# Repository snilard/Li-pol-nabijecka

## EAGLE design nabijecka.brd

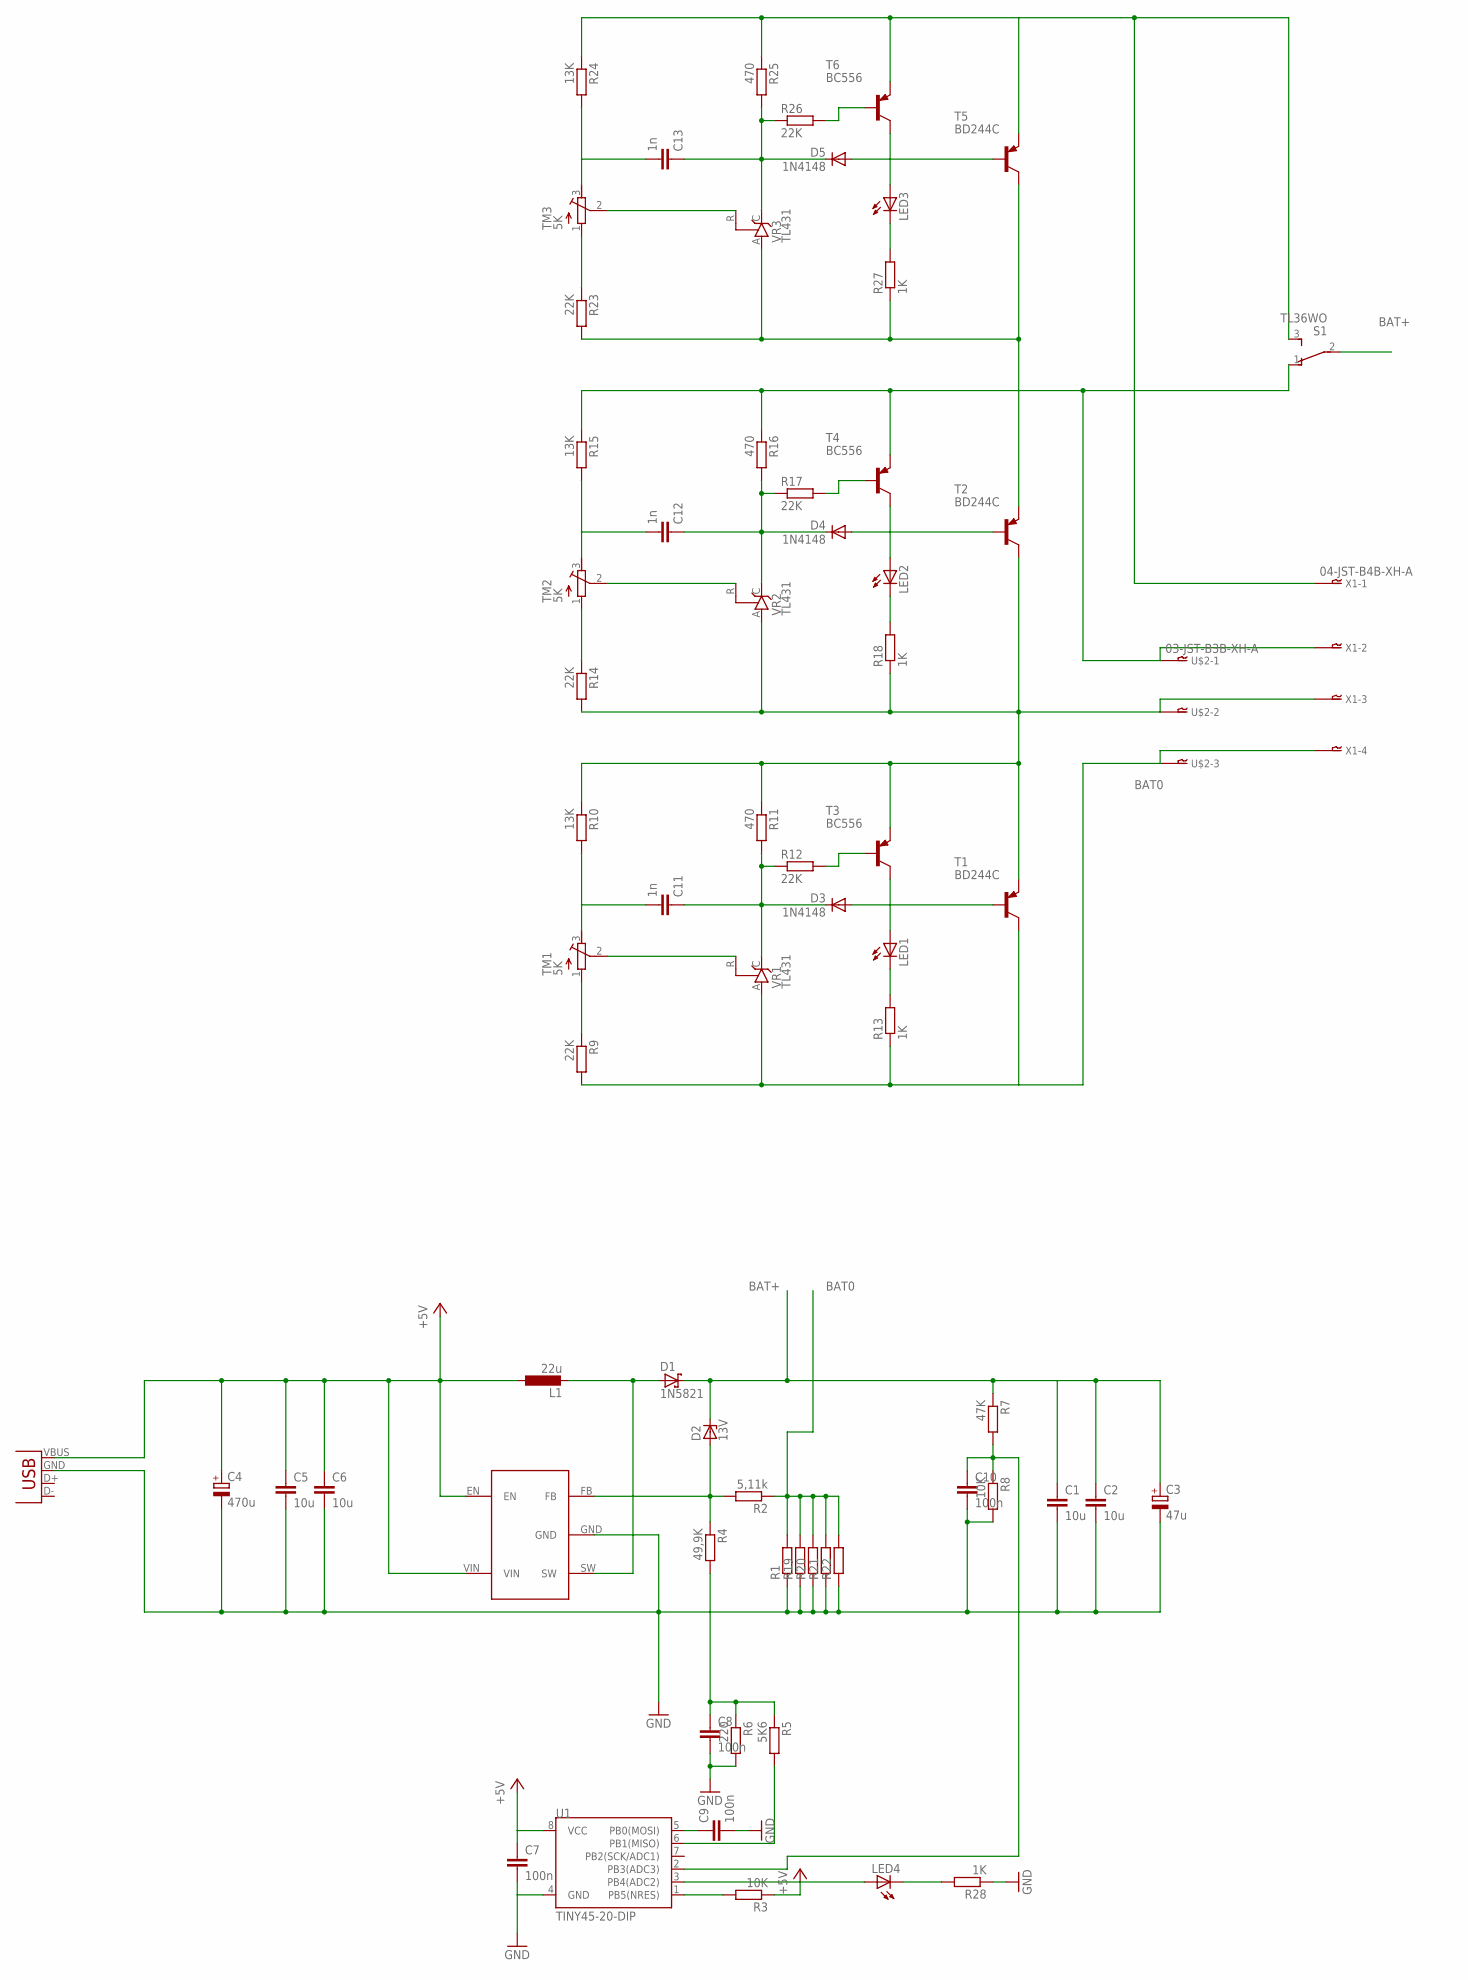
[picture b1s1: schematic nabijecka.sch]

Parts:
C1, C2, C5, C6: 10u; C1206
C3: 47u; E3,5-8
C4: 470u; E3,5-8
C7, C9: 100n; C0805
C8, C10: 100n; C1206
C11, C12, C13: 1n; C1206
D1: 1N5821; DO35-7
D2: 13V; SOD80C
D3, D4, D5: 1N4148; SOD80C
JP2: USB-A-H
L1: 22u; POWER-CHOKE_WE-TPC
LED1, LED2, LED3, LED4: LED3MM
R1, R19, R20, R21, R22: R-EU_0204/7; 0204/7
R2: 5,11k; 0204/5
R3: 10K; R0805
R4: 49,9K; 0204/5
R5: 5K6; R1206
R6: 220; R1206
R7: 47K; R1206
R8: 10K; R1206
R9, R14, R23: 22K; R1206
R10, R15, R24: 13K; R1206
R11, R16, R25: 470; R1206
R12, R17, R26: 22K; R0805
R13, R18, R27, R28: 1K; R1206
S1: TL36WO; TL3XWO
T1, T2, T5: BD244C; TO220
T3, T4, T6: BC556; TO92-EBC
TM1, TM2, TM3: 5K; RTRIM64P
U1: TINY45-20-DIP; DIP08
U$1: MIC2287
U$2: 03-JST-B3B-XH-A; B3B-XH
VR1, VR2, VR3: TL431; TO92-CLP
X1: 04-JST-B4B-XH-A; B4B-XH

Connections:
+5V: C4.+, C5.1, C6.1, C7.1, JP2.VBUS (GND), L1.1, R3.1, U1.8 (VCC), U$1.EN, U$1.VIN
BAT0: R1.2, R2.1, R9.2, R13.1, R19.2, R20.2, R21.2, R22.2, T1.2 (C), U$2.P$3, VR1.A, X1.P$4
BAT1: R10.1, R11.1, R14.2, R18.1, T1.3 (E), T2.2 (C), T3.E, U$2.P$2, VR2.A, X1.P$3
BAT2: R15.1, R16.1, R23.2, R27.1, S1.1 (O), T2.3 (E), T4.E, T5.2 (C), U$2.P$1, VR3.A, X1.P$2
BAT+: C1.1, C2.1, C3.+, D1.C, D2.C, R7.1, S1.2
GND: C1.2, C2.2, C3.-, C4.-, C5.2, C6.2, C7.2, C8.2, C9.2, C10.2, JP2.GND (VBUS), R1.1, R6.2, R8.2, R19.1, R20.1, R21.1, R22.1, R28.1, U1.4 (GND), U$1.GND
unnamed: C8.1, R4.2, R5.1, R6.1
unnamed: D1.A, L1.2, U$1.SW
unnamed: D2.A, R2.2, R4.1, U$1.FB
unnamed: R3.2, U1.1 (PB5(NRES))
unnamed: D3.A, T1.1 (B)
unnamed: R5.2, U1.6 (PB1(MISO))
unnamed: D4.A, T2.1 (B)
unnamed: C9.1, U1.5 (PB0(MOSI))
unnamed: C11.1, D3.C, R11.2, R12.1, VR1.C
unnamed: C10.1, R7.2, R8.1, U1.2 (PB3(ADC3))
unnamed: D5.A, T5.1 (B)
unnamed: C12.1, D4.C, R16.2, R17.1, VR2.C
unnamed: C11.2, R10.2, TM1.3 (A)
unnamed: TM1.2 (S), VR1.R
unnamed: R9.1, TM1.1 (E)
unnamed: LED1.K (C), R13.2
unnamed: C12.2, R15.2, TM2.3 (A)
unnamed: LED1.A, T3.C
unnamed: TM2.2 (S), VR2.R
unnamed: R12.2, T3.B
unnamed: C13.1, D5.C, R25.2, R26.1, VR3.C
unnamed: R14.1, TM2.1 (E)
unnamed: R17.2, T4.B
unnamed: LED2.K (C), R18.2
unnamed: LED2.A, T4.C
unnamed: C13.2, R24.2, TM3.3 (A)
unnamed: TM3.2 (S), VR3.R
unnamed: R23.1, TM3.1 (E)
unnamed: R26.2, T6.B
unnamed: LED3.K (C), R27.2
unnamed: LED3.A, T6.C
unnamed: R24.1, R25.1, S1.3 (S), T5.3 (E), T6.E, X1.P$1
unnamed: LED4.K (C), R28.2
unnamed: LED4.A, U1.3 (PB4(ADC2))

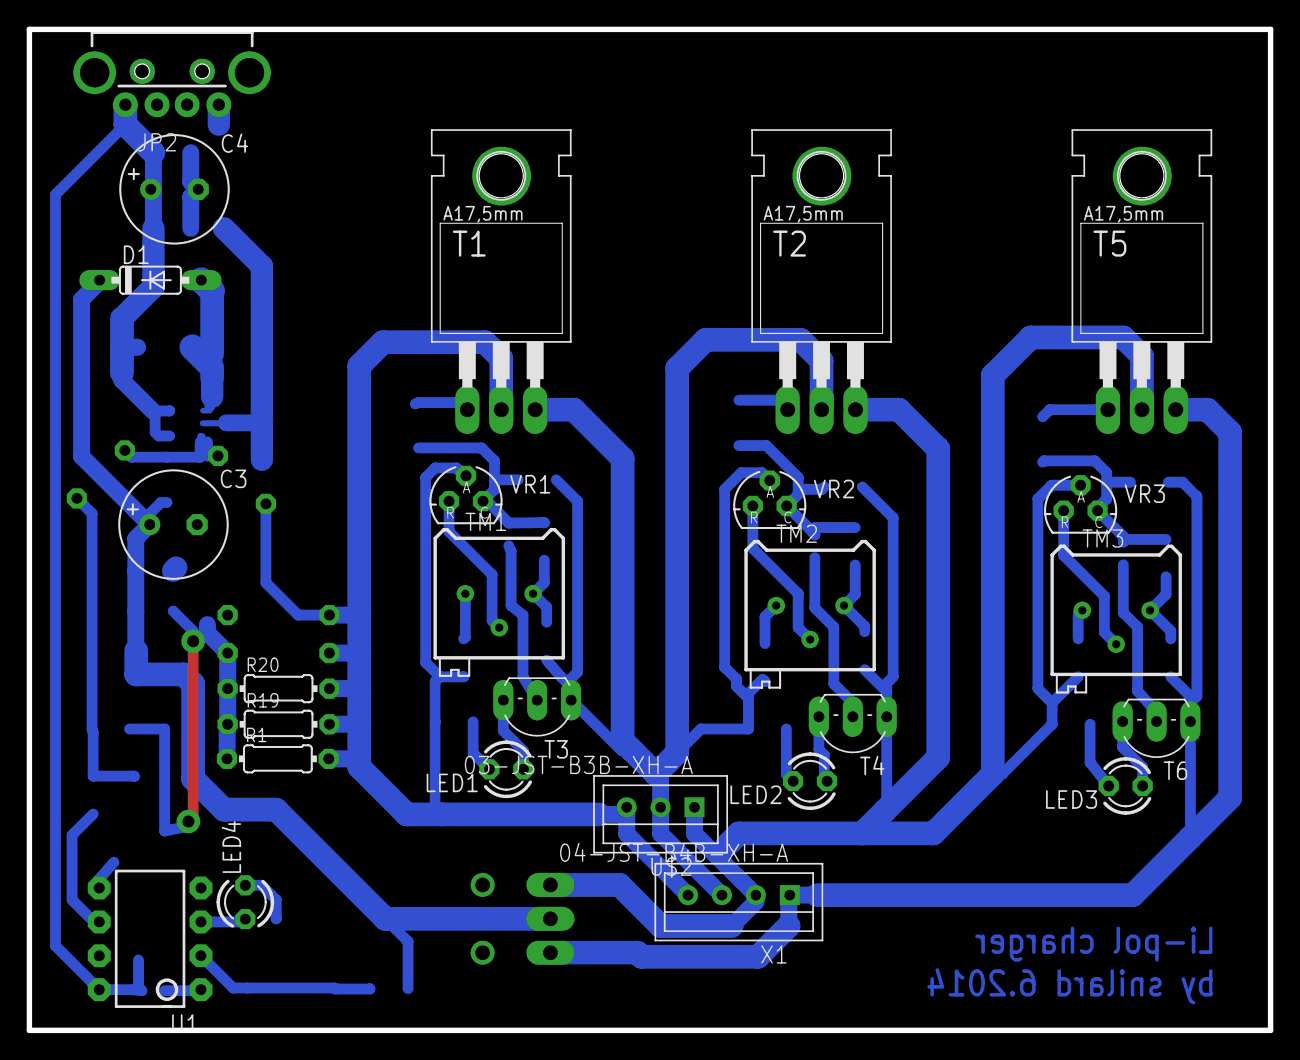
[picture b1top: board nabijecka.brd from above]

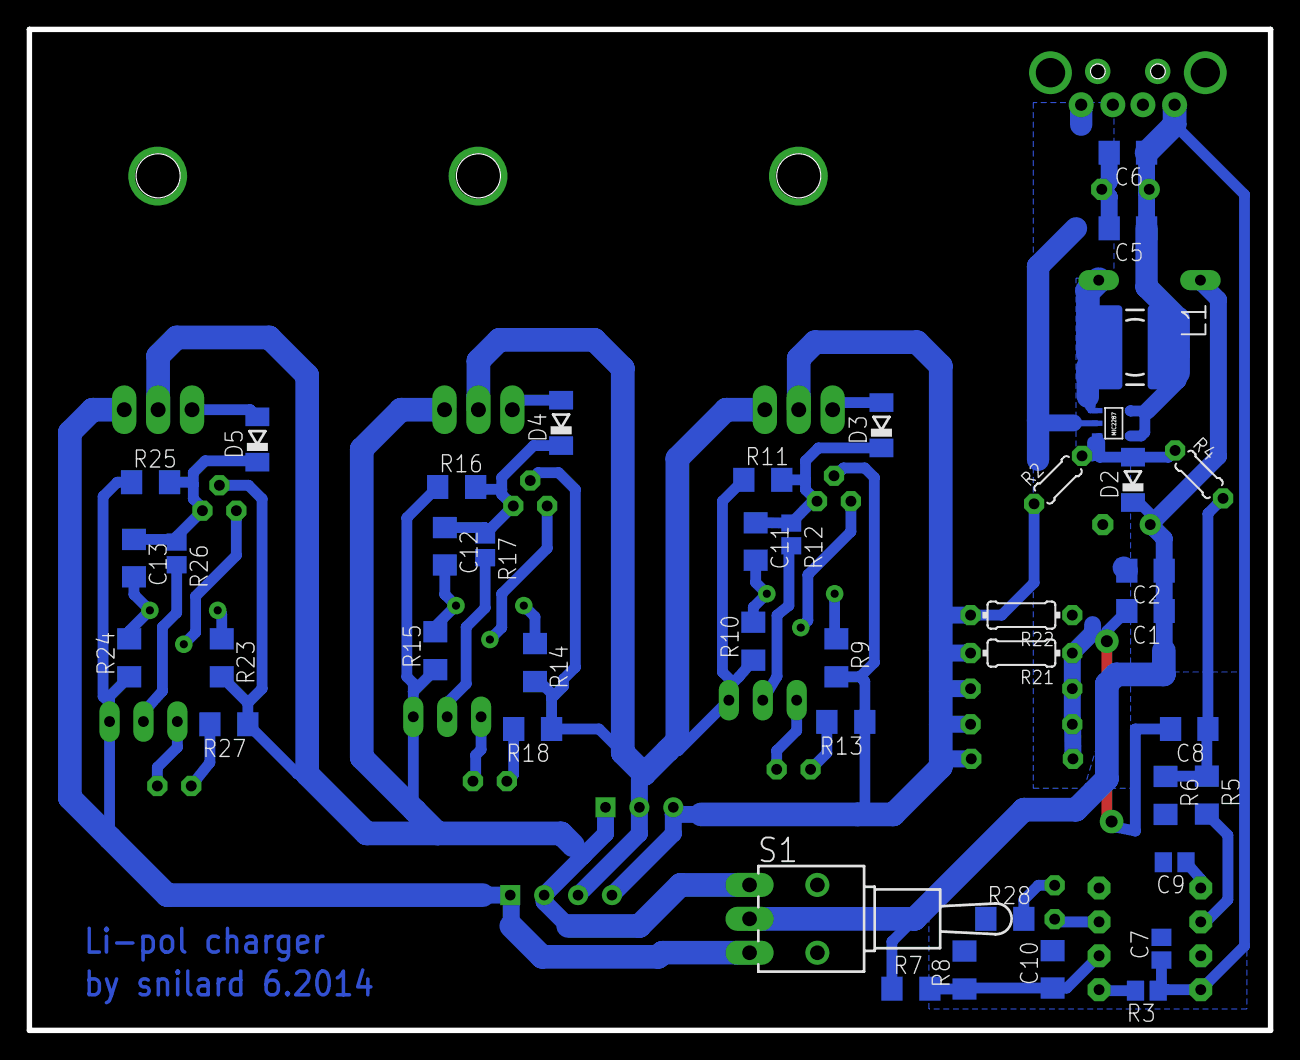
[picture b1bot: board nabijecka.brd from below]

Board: 2 copper layers, 93.0 x 75.0 mm, 69 parts (43 on the bottom side), 40 nets.

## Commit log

2014-06-21 Initial commit.
2014-06-21 Add first working code.
    Voltage on PB3 is measured periodically. LED is turned on if voltage exceed treshold. This will serve as indicator of charged battery. Every cycle PWM is decreaded if voltage is lower than treshold a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
2014-06-21 Add final circuit schematics and PCB layout.
2014-06-21 Add PCB template in PDF.
2014-07-02 Add 2S/3S battery recognition. Set voltages for 4,13 V per cell.
2014-07-02 Remove eagle.epf.
2014-07-02 Add schema in PDF. Rename files.
2014-11-16 Add periodic blinking. Change of charged indicator to current treshold.
2014-11-16 Formating.
2014-11-16 Changed target voltage to 4,17 V per cell.

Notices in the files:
parts and their libraries:
SparkFun-Connectors: Licensing: Creative Commons ShareAlike 4.0 International - https://creativecommons.org/licenses/by-sa/4.0
